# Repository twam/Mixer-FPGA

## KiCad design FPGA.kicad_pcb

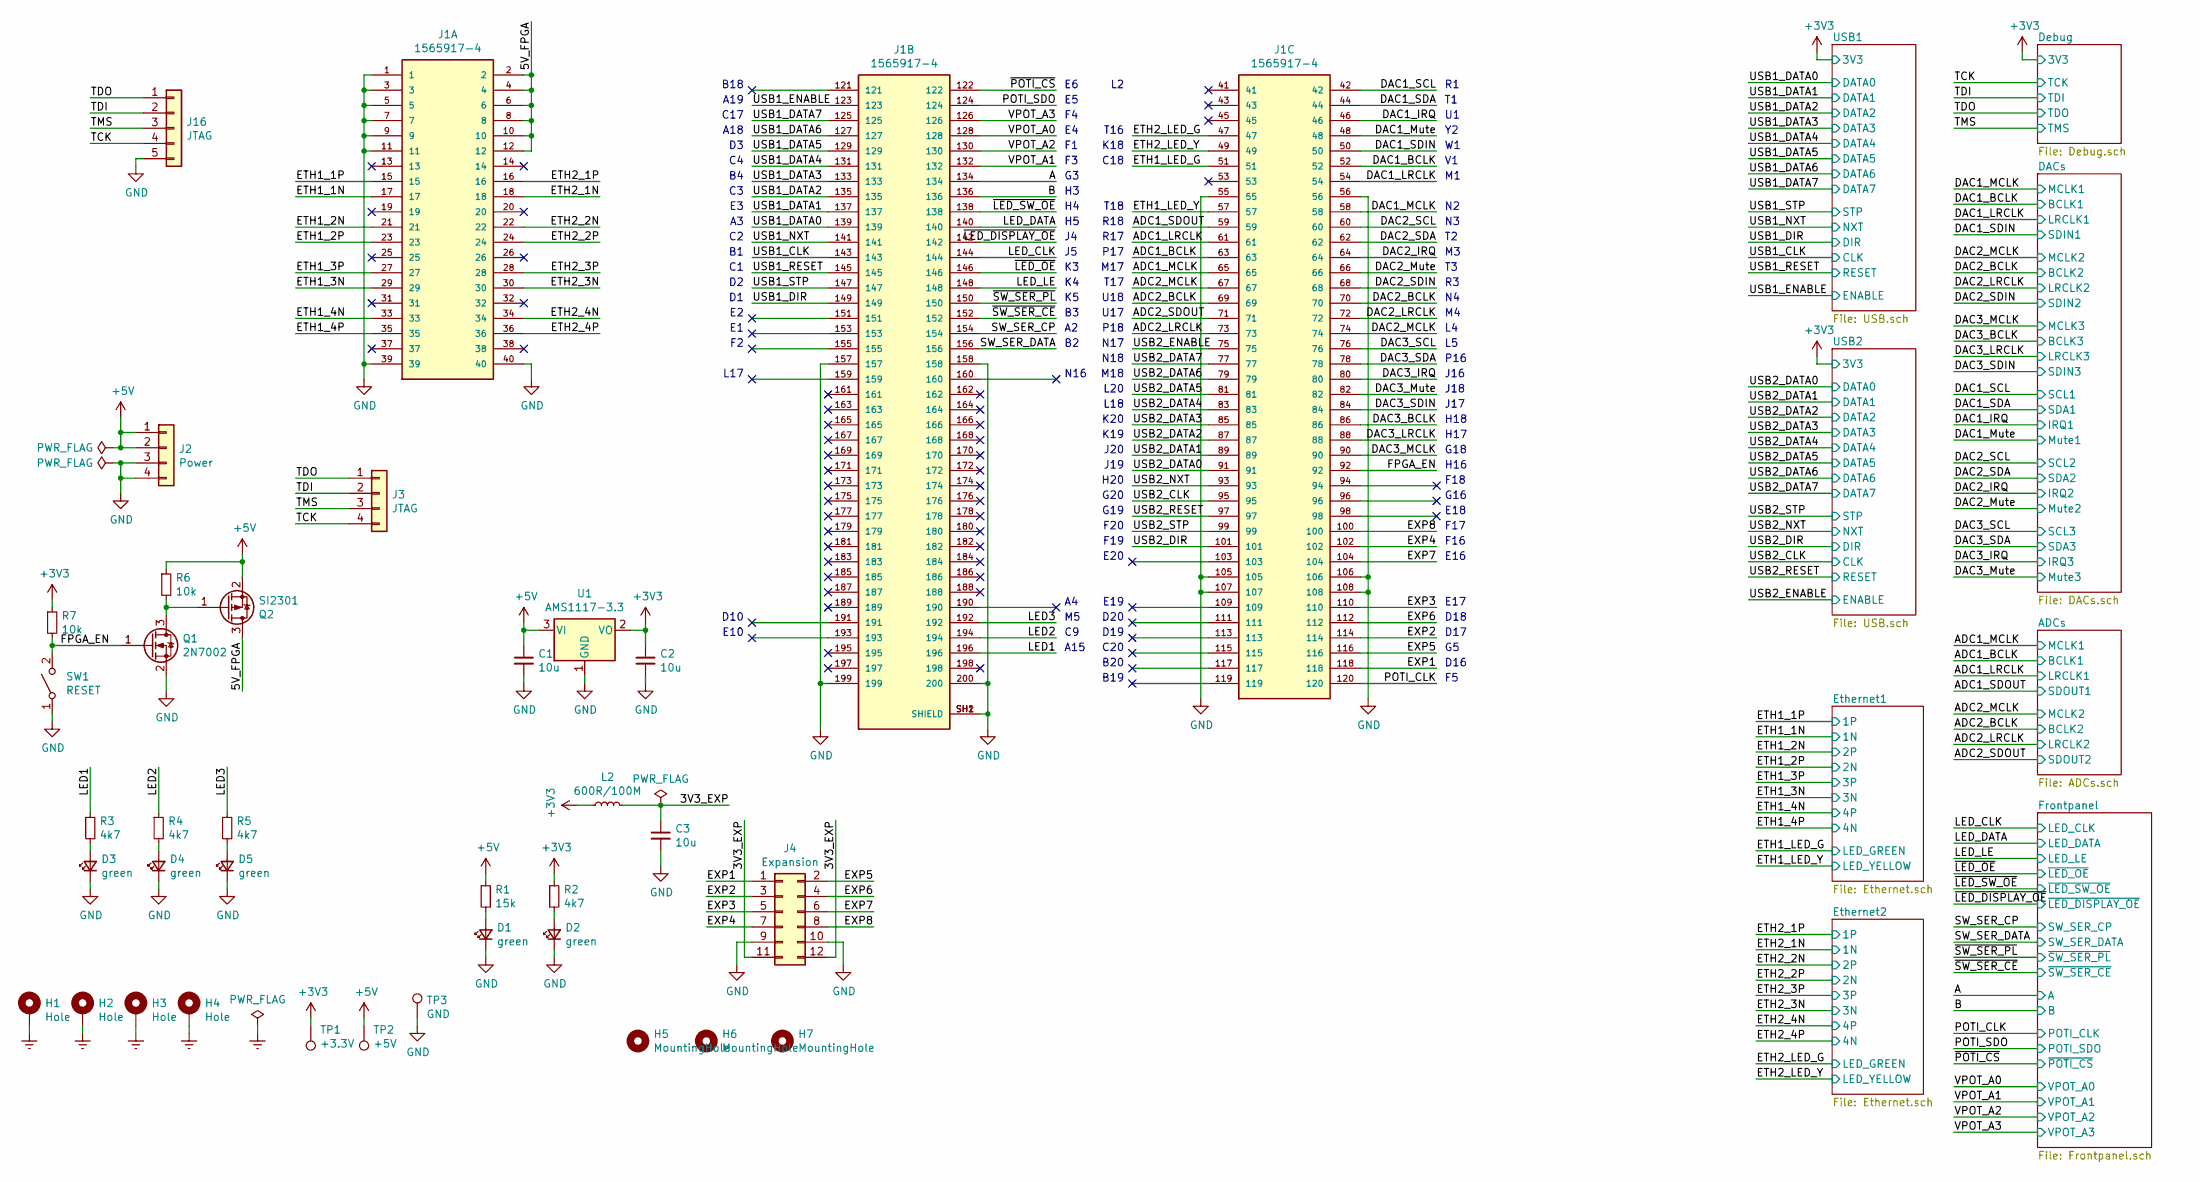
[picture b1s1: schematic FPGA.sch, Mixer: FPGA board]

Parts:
C1, C2, C3: 10u; C_0805_2012Metric; LCSC C15850
D1, D2, D3, D4, D5: green; LED_0603_1608Metric; LCSC C72043
H1, H2, H3, H4: Hole; MountingHole_2.7mm_M2.5_DIN965_Pad
H5, H6, H7: MountingHole; MountingHole_JLCPCB
J1: 1565917-4; TE_1565917-4
J2: Power; JST_VH_B4P-VH_1x04_P3.96mm_Vertical
J3: JTAG; PinHeader_1x04_P2.54mm_Vertical
J4: Expansion; PinHeader_2x06_P2.54mm_Vertical
J16: JTAG; PinHeader_1x05_P2.54mm_Vertical
L2: 600R/100M; L_0805_2012Metric; LCSC C1017
Q1: 2N7002; SOT-23; LCSC C8545
Q2: SI2301; SOT-23; LCSC C10487
R1: 15k; R_0603_1608Metric; LCSC C22809
R2, R3, R4, R5: 4k7; R_0603_1608Metric; LCSC C23162
R6, R7: 10k; R_0603_1608Metric; LCSC C25804
SW1: RESET; SW_SPST_XKB_TS-1187A-X-X-X; LCSC C318884
TP1: +3.3V; TestPoint_Pad_D1.5mm
TP2: +5V; TestPoint_Pad_D1.5mm
TP3: GND; TestPoint_Pad_D1.5mm
U1: AMS1117-3.3; SOT-223-3_TabPin2; LCSC C6186

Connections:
+3V3: C2.1, L2.1, R2.1, R7.1, TP1.1, U1.2 (VO); also elsewhere on the board
+5V: C1.1, J2.1, J2.2, Q2.2 (S), R1.1, R6.1, TP2.1, U1.3 (VI)
/3V3_EXP: C3.1, J4.11, J4.12, L2.2
/5V_FPGA: J1.2, J1.4, J1.6, J1.8, J1.10, J1.12, Q2.3 (D)
/A: J1.134; also elsewhere on the board
/ADC1_BCLK: J1.63; also elsewhere on the board
/ADC1_LRCLK: J1.61; also elsewhere on the board
/ADC1_MCLK: J1.65; also elsewhere on the board
/ADC1_SDOUT: J1.59; also elsewhere on the board
/ADC2_BCLK: J1.69; also elsewhere on the board
/ADC2_LRCLK: J1.73; also elsewhere on the board
/ADC2_MCLK: J1.67; also elsewhere on the board
/ADC2_SDOUT: J1.71; also elsewhere on the board
/B: J1.136; also elsewhere on the board
/DAC1_BCLK: J1.52; also elsewhere on the board
/DAC1_IRQ: J1.46; also elsewhere on the board
/DAC1_LRCLK: J1.54; also elsewhere on the board
/DAC1_MCLK: J1.58; also elsewhere on the board
/DAC1_Mute: J1.48; also elsewhere on the board
/DAC1_SCL: J1.42; also elsewhere on the board
/DAC1_SDA: J1.44; also elsewhere on the board
/DAC1_SDIN: J1.50; also elsewhere on the board
/DAC2_BCLK: J1.70; also elsewhere on the board
/DAC2_IRQ: J1.64; also elsewhere on the board
/DAC2_LRCLK: J1.72; also elsewhere on the board
/DAC2_MCLK: J1.74; also elsewhere on the board
/DAC2_Mute: J1.66; also elsewhere on the board
/DAC2_SCL: J1.60; also elsewhere on the board
/DAC2_SDA: J1.62; also elsewhere on the board
/DAC2_SDIN: J1.68; also elsewhere on the board
/DAC3_BCLK: J1.86; also elsewhere on the board
/DAC3_IRQ: J1.80; also elsewhere on the board
/DAC3_LRCLK: J1.88; also elsewhere on the board
/DAC3_MCLK: J1.90; also elsewhere on the board
/DAC3_Mute: J1.82; also elsewhere on the board
/DAC3_SCL: J1.76; also elsewhere on the board
/DAC3_SDA: J1.78; also elsewhere on the board
/DAC3_SDIN: J1.84; also elsewhere on the board
/ETH1_1N: J1.17; also elsewhere on the board
/ETH1_1P: J1.15; also elsewhere on the board
/ETH1_2N: J1.21; also elsewhere on the board
/ETH1_2P: J1.23; also elsewhere on the board
/ETH1_3N: J1.29; also elsewhere on the board
/ETH1_3P: J1.27; also elsewhere on the board
/ETH1_4N: J1.33; also elsewhere on the board
/ETH1_4P: J1.35; also elsewhere on the board
/ETH1_LED_G: J1.51; also elsewhere on the board
/ETH1_LED_Y: J1.57; also elsewhere on the board
/ETH2_1N: J1.18; also elsewhere on the board
/ETH2_1P: J1.16; also elsewhere on the board
/ETH2_2N: J1.22; also elsewhere on the board
/ETH2_2P: J1.24; also elsewhere on the board
/ETH2_3N: J1.30; also elsewhere on the board
/ETH2_3P: J1.28; also elsewhere on the board
/ETH2_4N: J1.34; also elsewhere on the board
/ETH2_4P: J1.36; also elsewhere on the board
/ETH2_LED_G: J1.47; also elsewhere on the board
/ETH2_LED_Y: J1.49; also elsewhere on the board
/EXP1: J1.118, J4.1
/EXP2: J1.114, J4.3
/EXP3: J1.110, J4.5
/EXP4: J1.102, J4.7
/EXP5: J1.116, J4.2
/EXP6: J1.112, J4.4
/EXP7: J1.104, J4.6
/EXP8: J1.100, J4.8
/FPGA_EN: J1.92, Q1.1 (G), R7.2, SW1.2 (B)
/LED1: J1.196, R3.1
/LED2: J1.194, R4.1
/LED3: J1.192, R5.1
/LED_CLK: J1.144; also elsewhere on the board
/LED_DATA: J1.140; also elsewhere on the board
/LED_LE: J1.148; also elsewhere on the board
/POTI_CLK: J1.120; also elsewhere on the board
/POTI_SDO: J1.124; also elsewhere on the board
/SW_SER_CP: J1.154; also elsewhere on the board
/SW_SER_DATA: J1.156; also elsewhere on the board
/TCK: J3.4, J16.4; also elsewhere on the board
/TDI: J3.2, J16.2; also elsewhere on the board
/TDO: J3.1, J16.1; also elsewhere on the board
/TMS: J3.3, J16.3; also elsewhere on the board
/USB1_CLK: J1.143; also elsewhere on the board
/USB1_DATA0: J1.139; also elsewhere on the board
/USB1_DATA1: J1.137; also elsewhere on the board
/USB1_DATA2: J1.135; also elsewhere on the board
/USB1_DATA3: J1.133; also elsewhere on the board
/USB1_DATA4: J1.131; also elsewhere on the board
/USB1_DATA5: J1.129; also elsewhere on the board
/USB1_DATA6: J1.127; also elsewhere on the board
/USB1_DATA7: J1.125; also elsewhere on the board
/USB1_DIR: J1.149; also elsewhere on the board
/USB1_ENABLE: J1.123; also elsewhere on the board
/USB1_NXT: J1.141; also elsewhere on the board
/USB1_RESET: J1.145; also elsewhere on the board
/USB1_STP: J1.147; also elsewhere on the board
/USB2_CLK: J1.95; also elsewhere on the board
/USB2_DATA0: J1.91; also elsewhere on the board
/USB2_DATA1: J1.89; also elsewhere on the board
/USB2_DATA2: J1.87; also elsewhere on the board
/USB2_DATA3: J1.85; also elsewhere on the board
/USB2_DATA4: J1.83; also elsewhere on the board
/USB2_DATA5: J1.81; also elsewhere on the board
/USB2_DATA6: J1.79; also elsewhere on the board
/USB2_DATA7: J1.77; also elsewhere on the board
/USB2_DIR: J1.101; also elsewhere on the board
/USB2_ENABLE: J1.75; also elsewhere on the board
/USB2_NXT: J1.93; also elsewhere on the board
/USB2_RESET: J1.97; also elsewhere on the board
/USB2_STP: J1.99; also elsewhere on the board
/VPOT_A0: J1.128; also elsewhere on the board
/VPOT_A1: J1.132; also elsewhere on the board
/VPOT_A2: J1.130; also elsewhere on the board
/VPOT_A3: J1.126; also elsewhere on the board
/~LED_DISPLAY_OE: J1.142; also elsewhere on the board
/~LED_OE: J1.146; also elsewhere on the board
/~LED_SW_OE: J1.138; also elsewhere on the board
/~POTI_CS: J1.122; also elsewhere on the board
/~SW_SER_CE: J1.152; also elsewhere on the board
/~SW_SER_PL: J1.150; also elsewhere on the board
Earth: H1.1, H2.1, H3.1, H4.1; also elsewhere on the board
GND: C1.2, C2.2, C3.2, D1.1 (K), D2.1 (K), D3.1 (K), D4.1 (K), D5.1 (K), J1.1, J1.3, J1.5, J1.7, J1.9, J1.11, J1.39, J1.40, J1.55, J1.56, J1.105, J1.106, J1.107, J1.108, J1.157, J1.158, J1.199, J1.200, J1.SH1 (SHIELD), J1.SH2 (SHIELD), J2.3, J2.4, J4.9, J4.10, J16.5, Q1.2 (S), SW1.1 (A), TP3.1, U1.1 (GND); also elsewhere on the board
unnamed: D1.2 (A), R1.2
unnamed: D2.2 (A), R2.2
unnamed: D3.2 (A), R3.2
unnamed: D4.2 (A), R4.2
unnamed: D5.2 (A), R5.2
unnamed: Q1.3 (D), Q2.1 (G), R6.2

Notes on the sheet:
K18
C18
T18
R18
R17
P17
M17
T17
U18
U17
P18
N17
N18
M18
L20
L18
K20
K19
J20
J19
H20
G20
G19
F20
F19
E20
E19
D20
D19
C20
B20
B19
D16
D17
D18
E17
E16
F16
F17
E18

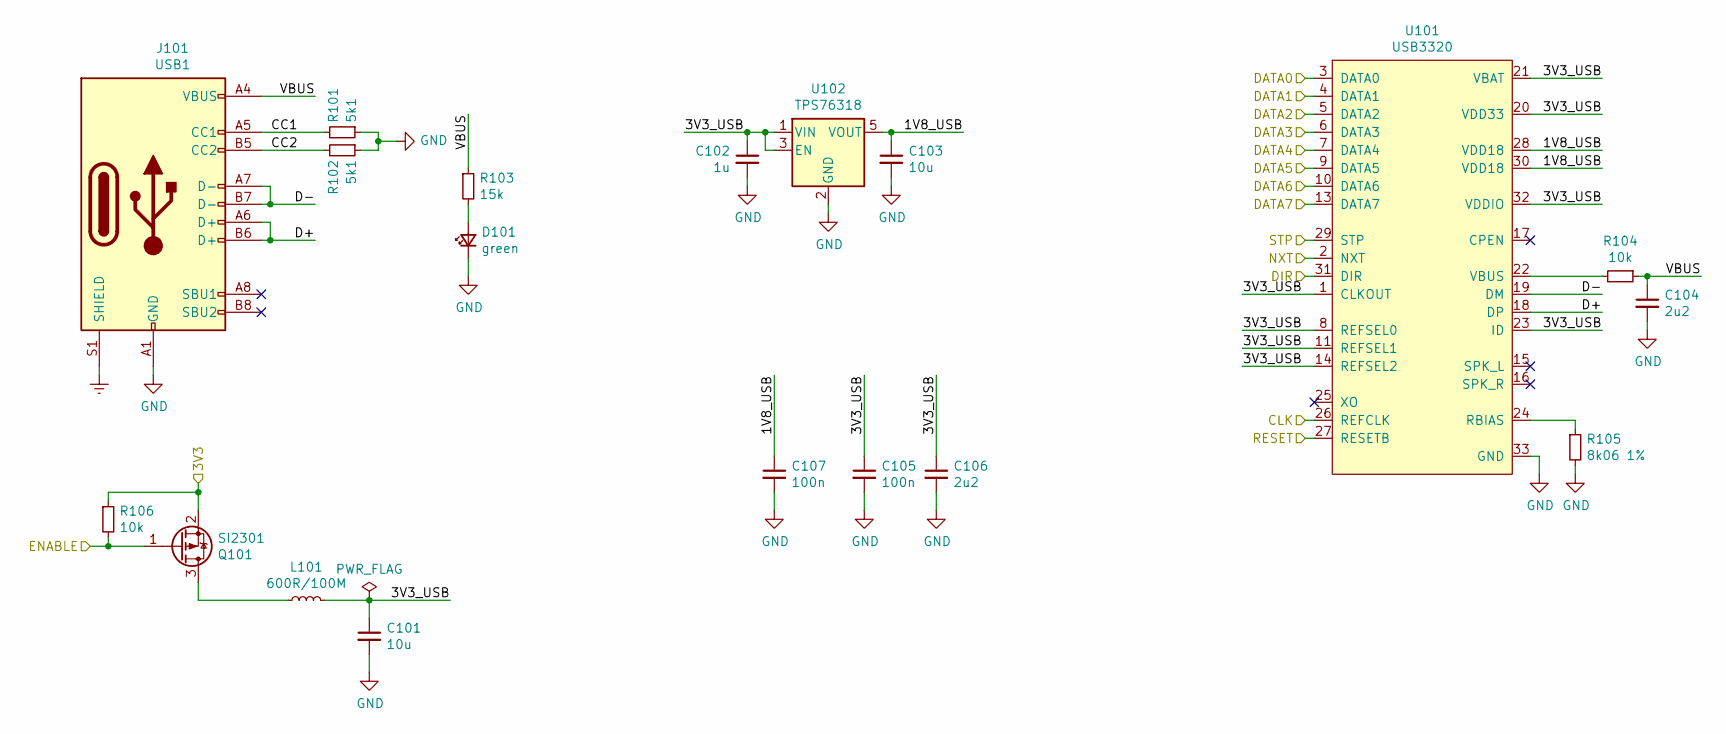
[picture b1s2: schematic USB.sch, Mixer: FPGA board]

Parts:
C101: 10u; C_0805_2012Metric; LCSC C15850
C102: 1u; C_0603_1608Metric; LCSC C15849
C103: 10u; C_0603_1608Metric; LCSC C19702
C104, C106: 2u2; C_0603_1608Metric; LCSC C23630
C105, C107: 100n; C_0603_1608Metric; LCSC C14663
D101: green; LED_0603_1608Metric; LCSC C72043
J101: USB1; USB_C_Receptacle_XKB_U262-16XN-4BVC11; LCSC C165948
L101: 600R/100M; L_0805_2012Metric; LCSC C1017
Q101: SI2301; SOT-23; LCSC C10487
R101, R102: 5k1; R_0603_1608Metric; LCSC C23186
R103: 15k; R_0603_1608Metric; LCSC C22809
R104, R106: 10k; R_0603_1608Metric; LCSC C25804
R105: 8k06 1%; R_0603_1608Metric; LCSC C23112
U101: USB3320; QFN-32-1EP_5x5mm_P0.5mm_EP3.3x3.3mm; LCSC C132156
U102: TPS76318; SOT-23-5; LCSC C7099

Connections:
+3V3: Q101.2 (S), R106.1; also elsewhere on the board
/USB1/1V8_USB: C103.1, C107.1, U101.28 (VDD18), U101.30 (VDD18), U102.5 (VOUT)
/USB1/3V3_USB: C101.1, C102.1, C105.1, C106.1, L101.2, U101.1 (CLKOUT), U101.8 (REFSEL0), U101.11 (REFSEL1), U101.14 (REFSEL2), U101.20 (VDD33), U101.21 (VBAT), U101.23 (ID), U101.32 (VDDIO), U102.1 (VIN), U102.3 (EN)
/USB1/CC1: J101.A5 (CC1), R101.2
/USB1/CC2: J101.B5 (CC2), R102.2
/USB1/D+: J101.A6 (D+), J101.B6 (D+), U101.18 (DP)
/USB1/D-: J101.A7 (D-), J101.B7 (D-), U101.19 (DM)
/USB1/VBUS: C104.1, J101.A4 (VBUS), J101.A9 (VBUS), J101.B4 (VBUS), J101.B9 (VBUS), R103.1, R104.1
/USB1_CLK: U101.26 (REFCLK); also elsewhere on the board
/USB1_DATA0: U101.3 (DATA0); also elsewhere on the board
/USB1_DATA1: U101.4 (DATA1); also elsewhere on the board
/USB1_DATA2: U101.5 (DATA2); also elsewhere on the board
/USB1_DATA3: U101.6 (DATA3); also elsewhere on the board
/USB1_DATA4: U101.7 (DATA4); also elsewhere on the board
/USB1_DATA5: U101.9 (DATA5); also elsewhere on the board
/USB1_DATA6: U101.10 (DATA6); also elsewhere on the board
/USB1_DATA7: U101.13 (DATA7); also elsewhere on the board
/USB1_DIR: U101.31 (DIR); also elsewhere on the board
/USB1_ENABLE: Q101.1 (G), R106.2; also elsewhere on the board
/USB1_NXT: U101.2 (NXT); also elsewhere on the board
/USB1_RESET: U101.27 (RESETB); also elsewhere on the board
/USB1_STP: U101.29 (STP); also elsewhere on the board
Earth: J101.S1 (SHIELD); also elsewhere on the board
GND: C101.2, C102.2, C103.2, C104.2, C105.2, C106.2, C107.2, D101.1 (K), J101.A1 (GND), J101.A12 (GND), J101.B1 (GND), J101.B12 (GND), R101.1, R102.1, R105.2, U101.33 (GND), U102.2 (GND); also elsewhere on the board
unnamed: D101.2 (A), R103.2
unnamed: L101.1, Q101.3 (D)
unnamed: R104.2, U101.22 (VBUS)
unnamed: R105.1, U101.24 (RBIAS)

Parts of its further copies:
C201: 10u; C_0805_2012Metric; LCSC C15850
C202: 1u; C_0603_1608Metric; LCSC C15849
C203: 10u; C_0603_1608Metric; LCSC C19702
C204, C206: 2u2; C_0603_1608Metric; LCSC C23630
C205, C207: 100n; C_0603_1608Metric; LCSC C14663
D201: green; LED_0603_1608Metric; LCSC C72043
J201: USB1; USB_C_Receptacle_XKB_U262-16XN-4BVC11; LCSC C165948
L201: 600R/100M; L_0805_2012Metric; LCSC C1017
Q201: SI2301; SOT-23; LCSC C10487
R201, R202: 5k1; R_0603_1608Metric; LCSC C23186
R203: 15k; R_0603_1608Metric; LCSC C22809
R204, R206: 10k; R_0603_1608Metric; LCSC C25804
R205: 8k06 1%; R_0603_1608Metric; LCSC C23112
U201: USB3320; QFN-32-1EP_5x5mm_P0.5mm_EP3.3x3.3mm; LCSC C132156
U202: TPS76318; SOT-23-5; LCSC C7099

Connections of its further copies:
+3V3: Q201.2 (S), R206.1; also elsewhere on the board
/USB2/1V8_USB: C203.1, C207.1, U201.28 (VDD18), U201.30 (VDD18), U202.5 (VOUT)
/USB2/3V3_USB: C201.1, C202.1, C205.1, C206.1, L201.2, U201.1 (CLKOUT), U201.8 (REFSEL0), U201.11 (REFSEL1), U201.14 (REFSEL2), U201.20 (VDD33), U201.21 (VBAT), U201.23 (ID), U201.32 (VDDIO), U202.1 (VIN), U202.3 (EN)
/USB2/CC1: J201.A5 (CC1), R201.2
/USB2/CC2: J201.B5 (CC2), R202.2
/USB2/D+: J201.A6 (D+), J201.B6 (D+), U201.18 (DP)
/USB2/D-: J201.A7 (D-), J201.B7 (D-), U201.19 (DM)
/USB2/VBUS: C204.1, J201.A4 (VBUS), J201.A9 (VBUS), J201.B4 (VBUS), J201.B9 (VBUS), R203.1, R204.1
/USB2_CLK: U201.26 (REFCLK); also elsewhere on the board
/USB2_DATA0: U201.3 (DATA0); also elsewhere on the board
/USB2_DATA1: U201.4 (DATA1); also elsewhere on the board
/USB2_DATA2: U201.5 (DATA2); also elsewhere on the board
/USB2_DATA3: U201.6 (DATA3); also elsewhere on the board
/USB2_DATA4: U201.7 (DATA4); also elsewhere on the board
/USB2_DATA5: U201.9 (DATA5); also elsewhere on the board
/USB2_DATA6: U201.10 (DATA6); also elsewhere on the board
/USB2_DATA7: U201.13 (DATA7); also elsewhere on the board
/USB2_DIR: U201.31 (DIR); also elsewhere on the board
/USB2_ENABLE: Q201.1 (G), R206.2; also elsewhere on the board
/USB2_NXT: U201.2 (NXT); also elsewhere on the board
/USB2_RESET: U201.27 (RESETB); also elsewhere on the board
/USB2_STP: U201.29 (STP); also elsewhere on the board
Earth: J201.S1 (SHIELD); also elsewhere on the board
GND: C201.2, C202.2, C203.2, C204.2, C205.2, C206.2, C207.2, D201.1 (K), J201.A1 (GND), J201.A12 (GND), J201.B1 (GND), J201.B12 (GND), R201.1, R202.1, R205.2, U201.33 (GND), U202.2 (GND); also elsewhere on the board
unnamed: D201.2 (A), R203.2
unnamed: L201.1, Q201.3 (D)
unnamed: R204.2, U201.22 (VBUS)
unnamed: R205.1, U201.24 (RBIAS)

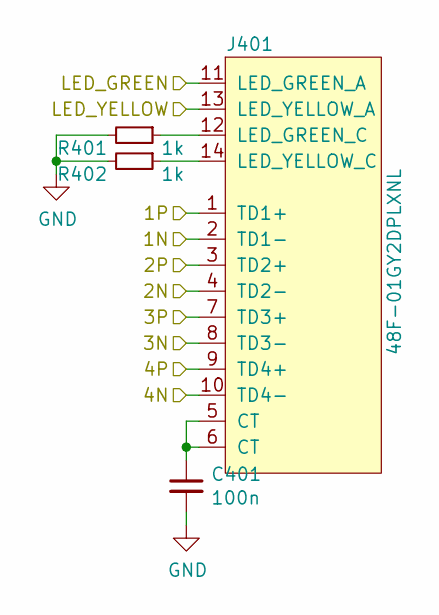
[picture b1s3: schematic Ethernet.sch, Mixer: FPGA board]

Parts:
C301: 100n; C_0603_1608Metric; LCSC C14663
J301: 48F-01GY2DPLXNL; LCSC C123172
R301, R302: 1k; R_0603_1608Metric; LCSC C21190

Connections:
/ETH1_1N: J301.2 (TD1-); also elsewhere on the board
/ETH1_1P: J301.1 (TD1+); also elsewhere on the board
/ETH1_2N: J301.3 (TD2+); also elsewhere on the board
/ETH1_2P: J301.4 (TD2-); also elsewhere on the board
/ETH1_3N: J301.8 (TD3-); also elsewhere on the board
/ETH1_3P: J301.7 (TD3+); also elsewhere on the board
/ETH1_4N: J301.9 (TD4+); also elsewhere on the board
/ETH1_4P: J301.10 (TD4-); also elsewhere on the board
/ETH1_LED_G: J301.11 (LED_GREEN_A); also elsewhere on the board
/ETH1_LED_Y: J301.13 (LED_YELLOW_A); also elsewhere on the board
GND: C301.2, R301.2, R302.2; also elsewhere on the board
unnamed: C301.1, J301.5 (CT), J301.6 (CT)
unnamed: J301.12 (LED_GREEN_C), R301.1
unnamed: J301.14 (LED_YELLOW_C), R302.1

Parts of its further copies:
C401: 100n; C_0603_1608Metric; LCSC C14663
J401: 48F-01GY2DPLXNL; LCSC C123172
R401, R402: 1k; R_0603_1608Metric; LCSC C21190

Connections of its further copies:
/ETH2_1N: J401.2 (TD1-); also elsewhere on the board
/ETH2_1P: J401.1 (TD1+); also elsewhere on the board
/ETH2_2N: J401.3 (TD2+); also elsewhere on the board
/ETH2_2P: J401.4 (TD2-); also elsewhere on the board
/ETH2_3N: J401.8 (TD3-); also elsewhere on the board
/ETH2_3P: J401.7 (TD3+); also elsewhere on the board
/ETH2_4N: J401.9 (TD4+); also elsewhere on the board
/ETH2_4P: J401.10 (TD4-); also elsewhere on the board
/ETH2_LED_G: J401.11 (LED_GREEN_A); also elsewhere on the board
/ETH2_LED_Y: J401.13 (LED_YELLOW_A); also elsewhere on the board
GND: C401.2, R401.2, R402.2; also elsewhere on the board
unnamed: C401.1, J401.5 (CT), J401.6 (CT)
unnamed: J401.12 (LED_GREEN_C), R401.1
unnamed: J401.14 (LED_YELLOW_C), R402.1

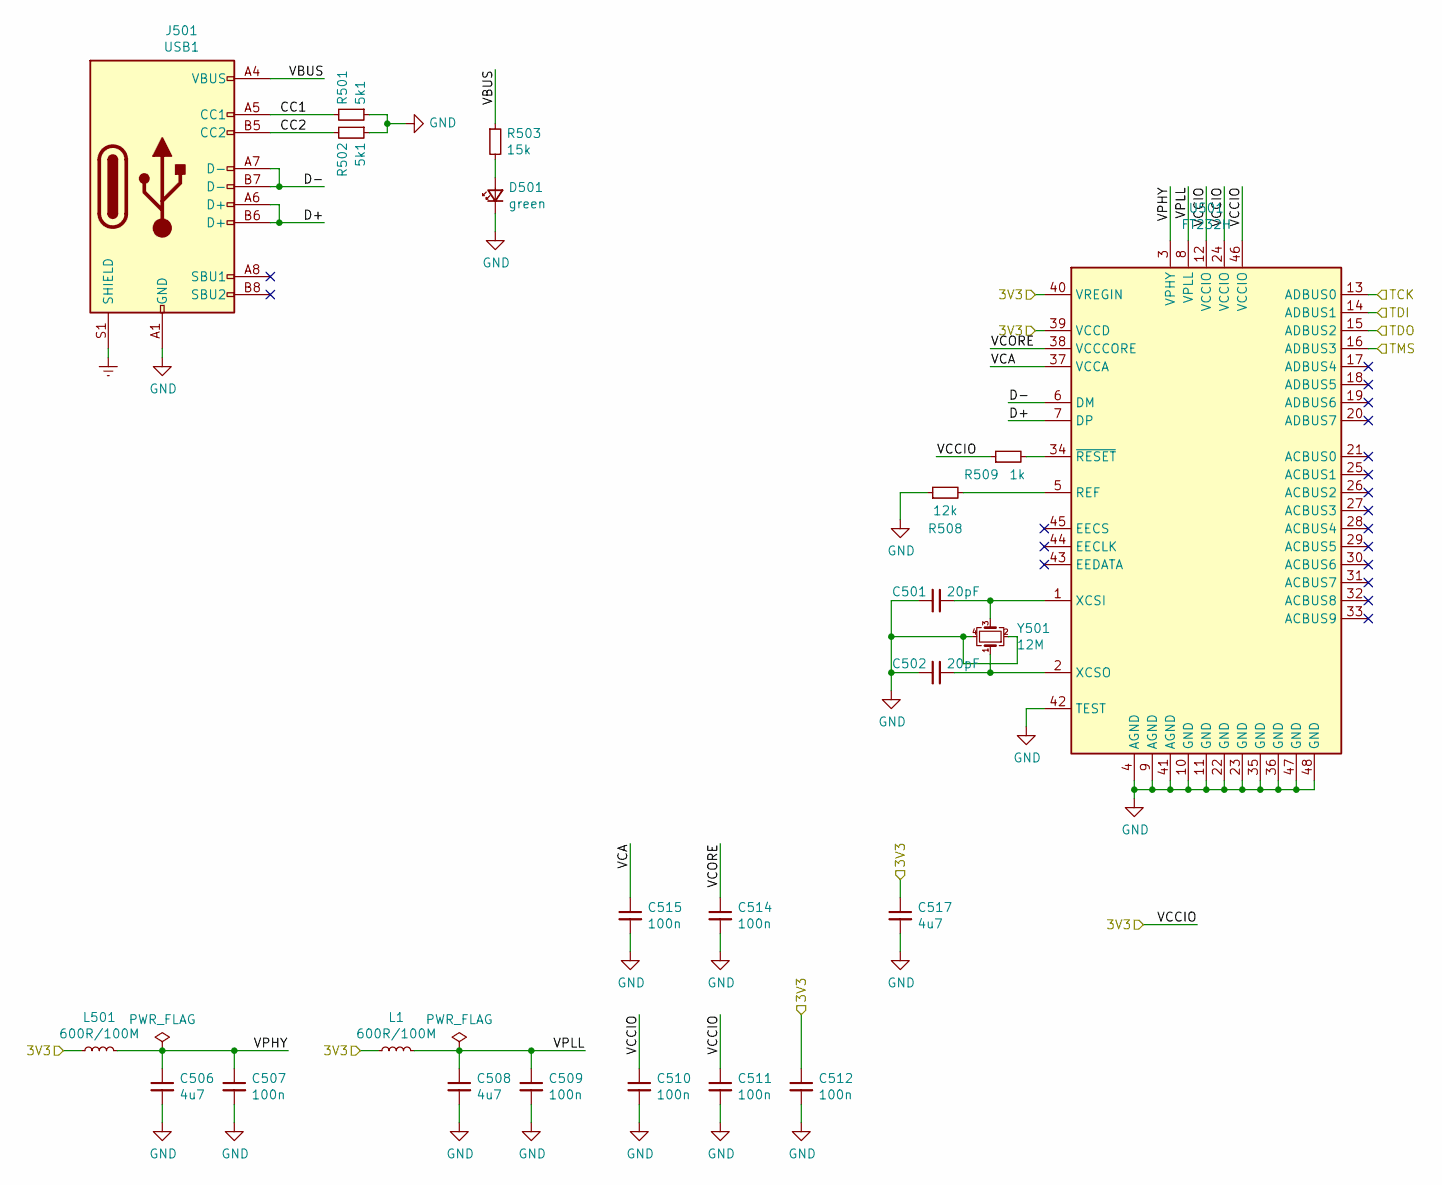
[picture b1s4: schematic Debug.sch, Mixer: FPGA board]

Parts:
C501, C502: 20pF; C_0603_1608Metric; LCSC C1648
C506, C508, C517: 4u7; C_0603_1608Metric; LCSC C19666
C507, C509, C510, C511, C512, C514, C515: 100n; C_0603_1608Metric; LCSC C14663
D501: green; LED_0603_1608Metric; LCSC C72043
J501: USB1; USB_C_Receptacle_XKB_U262-16XN-4BVC11; LCSC C165948
L1, L501: 600R/100M; L_0805_2012Metric; LCSC C1017
R501, R502: 5k1; R_0603_1608Metric; LCSC C23186
R503: 15k; R_0603_1608Metric; LCSC C22809
R508: 12k; R_0603_1608Metric; LCSC C22790
R509: 1k; R_0603_1608Metric; LCSC C21190
U501: FT232H; LQFP-48_7x7mm_P0.5mm; LCSC C51997
Y501: 12M; Crystal_SMD_3225-4Pin_3.2x2.5mm; LCSC C9002

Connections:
+3V3: C510.1, C511.1, C512.1, C517.1, L1.1, L501.1, R509.1, U501.12 (VCCIO), U501.24 (VCCIO), U501.39 (VCCD), U501.40 (VREGIN), U501.46 (VCCIO); also elsewhere on the board
/Debug/CC1: J501.A5 (CC1), R501.2
/Debug/CC2: J501.B5 (CC2), R502.2
/Debug/D+: J501.A6 (D+), J501.B6 (D+), U501.7 (DP)
/Debug/D-: J501.A7 (D-), J501.B7 (D-), U501.6 (DM)
/Debug/VBUS: J501.A4 (VBUS), J501.A9 (VBUS), J501.B4 (VBUS), J501.B9 (VBUS), R503.1
/Debug/VCA: C515.1, U501.37 (VCCA)
/Debug/VCORE: C514.1, U501.38 (VCCCORE)
/Debug/VPHY: C506.1, C507.1, L501.2, U501.3 (VPHY)
/Debug/VPLL: C508.1, C509.1, L1.2, U501.8 (VPLL)
/TCK: U501.13 (ADBUS0); also elsewhere on the board
/TDI: U501.14 (ADBUS1); also elsewhere on the board
/TDO: U501.15 (ADBUS2); also elsewhere on the board
/TMS: U501.16 (ADBUS3); also elsewhere on the board
Earth: J501.S1 (SHIELD); also elsewhere on the board
GND: C501.2, C502.2, C506.2, C507.2, C508.2, C509.2, C510.2, C511.2, C512.2, C514.2, C515.2, C517.2, D501.1 (K), J501.A1 (GND), J501.A12 (GND), J501.B1 (GND), J501.B12 (GND), R501.1, R502.1, R508.1, U501.4 (AGND), U501.9 (AGND), U501.10 (GND), U501.11 (GND), U501.22 (GND), U501.23 (GND), U501.35 (GND), U501.36 (GND), U501.41 (AGND), U501.42 (TEST), U501.47 (GND), U501.48 (GND), Y501.2, Y501.4; also elsewhere on the board
unnamed: C501.1, U501.1 (XCSI), Y501.3
unnamed: C502.1, U501.2 (XCSO), Y501.1
unnamed: D501.2 (A), R503.2
unnamed: R508.2, U501.5 (REF)
unnamed: R509.2, U501.34 (~RESET)

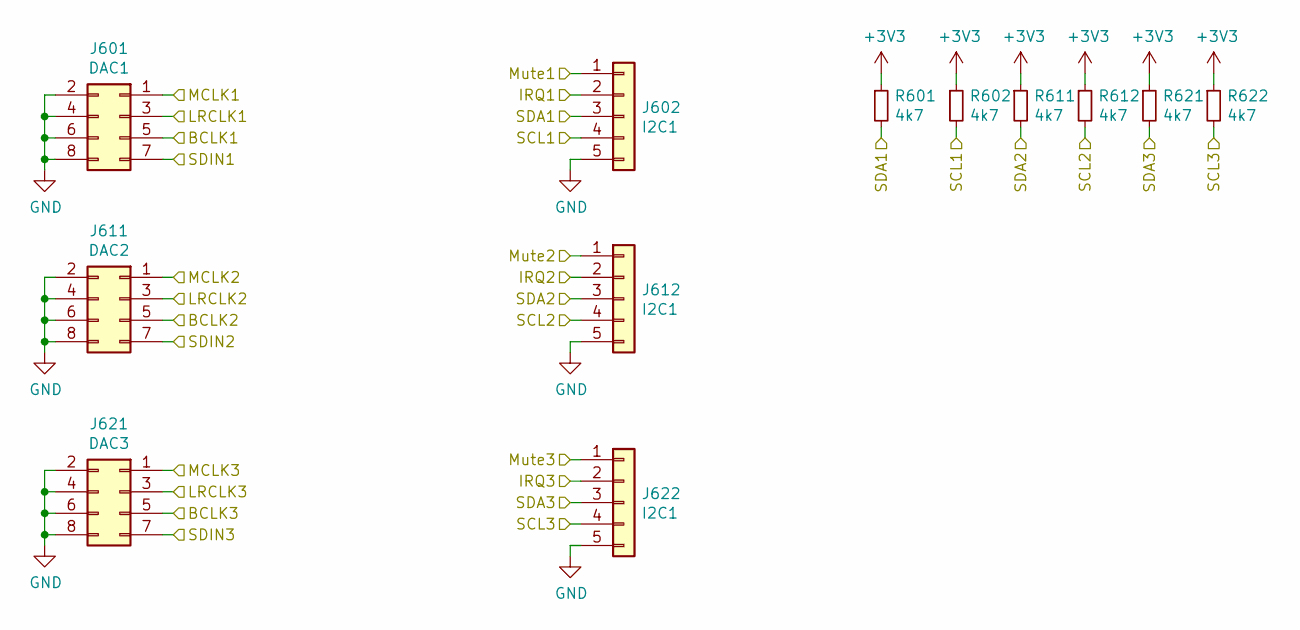
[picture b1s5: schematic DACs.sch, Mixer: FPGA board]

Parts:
J601: DAC1; PinHeader_2x04_P2.54mm_Vertical
J602, J612, J622: I2C1; PinHeader_1x05_P2.54mm_Vertical
J611: DAC2; PinHeader_2x04_P2.54mm_Vertical
J621: DAC3; PinHeader_2x04_P2.54mm_Vertical
R601, R602, R611, R612, R621, R622: 4k7; R_0603_1608Metric; LCSC C23162

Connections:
+3V3: R601.1, R602.1, R611.1, R612.1, R621.1, R622.1; also elsewhere on the board
/DAC1_BCLK: J601.5; also elsewhere on the board
/DAC1_IRQ: J602.2; also elsewhere on the board
/DAC1_LRCLK: J601.3; also elsewhere on the board
/DAC1_MCLK: J601.1; also elsewhere on the board
/DAC1_Mute: J602.1; also elsewhere on the board
/DAC1_SCL: J602.4, R602.2; also elsewhere on the board
/DAC1_SDA: J602.3, R601.2; also elsewhere on the board
/DAC1_SDIN: J601.7; also elsewhere on the board
/DAC2_BCLK: J611.5; also elsewhere on the board
/DAC2_IRQ: J612.2; also elsewhere on the board
/DAC2_LRCLK: J611.3; also elsewhere on the board
/DAC2_MCLK: J611.1; also elsewhere on the board
/DAC2_Mute: J612.1; also elsewhere on the board
/DAC2_SCL: J612.4, R612.2; also elsewhere on the board
/DAC2_SDA: J612.3, R611.2; also elsewhere on the board
/DAC2_SDIN: J611.7; also elsewhere on the board
/DAC3_BCLK: J621.5; also elsewhere on the board
/DAC3_IRQ: J622.2; also elsewhere on the board
/DAC3_LRCLK: J621.3; also elsewhere on the board
/DAC3_MCLK: J621.1; also elsewhere on the board
/DAC3_Mute: J622.1; also elsewhere on the board
/DAC3_SCL: J622.4, R622.2; also elsewhere on the board
/DAC3_SDA: J622.3, R621.2; also elsewhere on the board
/DAC3_SDIN: J621.7; also elsewhere on the board
GND: J601.2, J601.4, J601.6, J601.8, J602.5, J611.2, J611.4, J611.6, J611.8, J612.5, J621.2, J621.4, J621.6, J621.8, J622.5; also elsewhere on the board

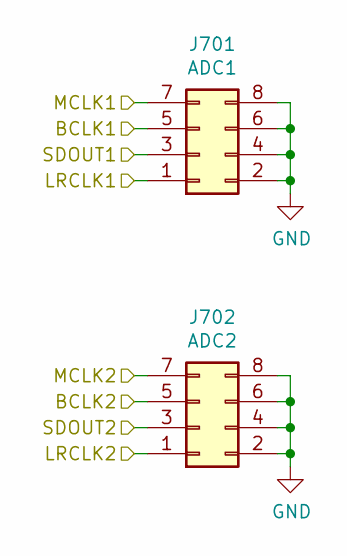
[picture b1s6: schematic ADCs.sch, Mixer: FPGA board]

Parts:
J701: ADC1; PinHeader_2x04_P2.54mm_Vertical
J702: ADC2; PinHeader_2x04_P2.54mm_Vertical

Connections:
/ADC1_BCLK: J701.5; also elsewhere on the board
/ADC1_LRCLK: J701.1; also elsewhere on the board
/ADC1_MCLK: J701.7; also elsewhere on the board
/ADC1_SDOUT: J701.3; also elsewhere on the board
/ADC2_BCLK: J702.5; also elsewhere on the board
/ADC2_LRCLK: J702.1; also elsewhere on the board
/ADC2_MCLK: J702.7; also elsewhere on the board
/ADC2_SDOUT: J702.3; also elsewhere on the board
GND: J701.2, J701.4, J701.6, J701.8, J702.2, J702.4, J702.6, J702.8; also elsewhere on the board

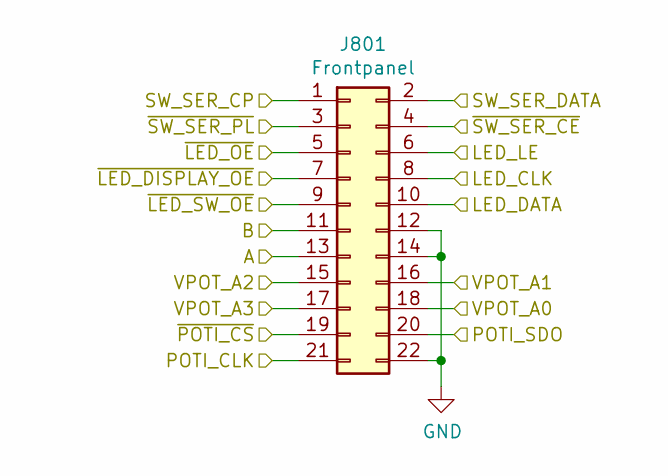
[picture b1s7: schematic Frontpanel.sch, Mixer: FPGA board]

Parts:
J801: Frontpanel; PinHeader_2x11_P2.54mm_Vertical

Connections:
/A: J801.13; also elsewhere on the board
/B: J801.11; also elsewhere on the board
/LED_CLK: J801.8; also elsewhere on the board
/LED_DATA: J801.10; also elsewhere on the board
/LED_LE: J801.6; also elsewhere on the board
/POTI_CLK: J801.21; also elsewhere on the board
/POTI_SDO: J801.20; also elsewhere on the board
/SW_SER_CP: J801.1; also elsewhere on the board
/SW_SER_DATA: J801.2; also elsewhere on the board
/VPOT_A0: J801.18; also elsewhere on the board
/VPOT_A1: J801.16; also elsewhere on the board
/VPOT_A2: J801.15; also elsewhere on the board
/VPOT_A3: J801.17; also elsewhere on the board
/~LED_DISPLAY_OE: J801.7; also elsewhere on the board
/~LED_OE: J801.5; also elsewhere on the board
/~LED_SW_OE: J801.9; also elsewhere on the board
/~POTI_CS: J801.19; also elsewhere on the board
/~SW_SER_CE: J801.4; also elsewhere on the board
/~SW_SER_PL: J801.3; also elsewhere on the board
GND: J801.12, J801.14, J801.22; also elsewhere on the board

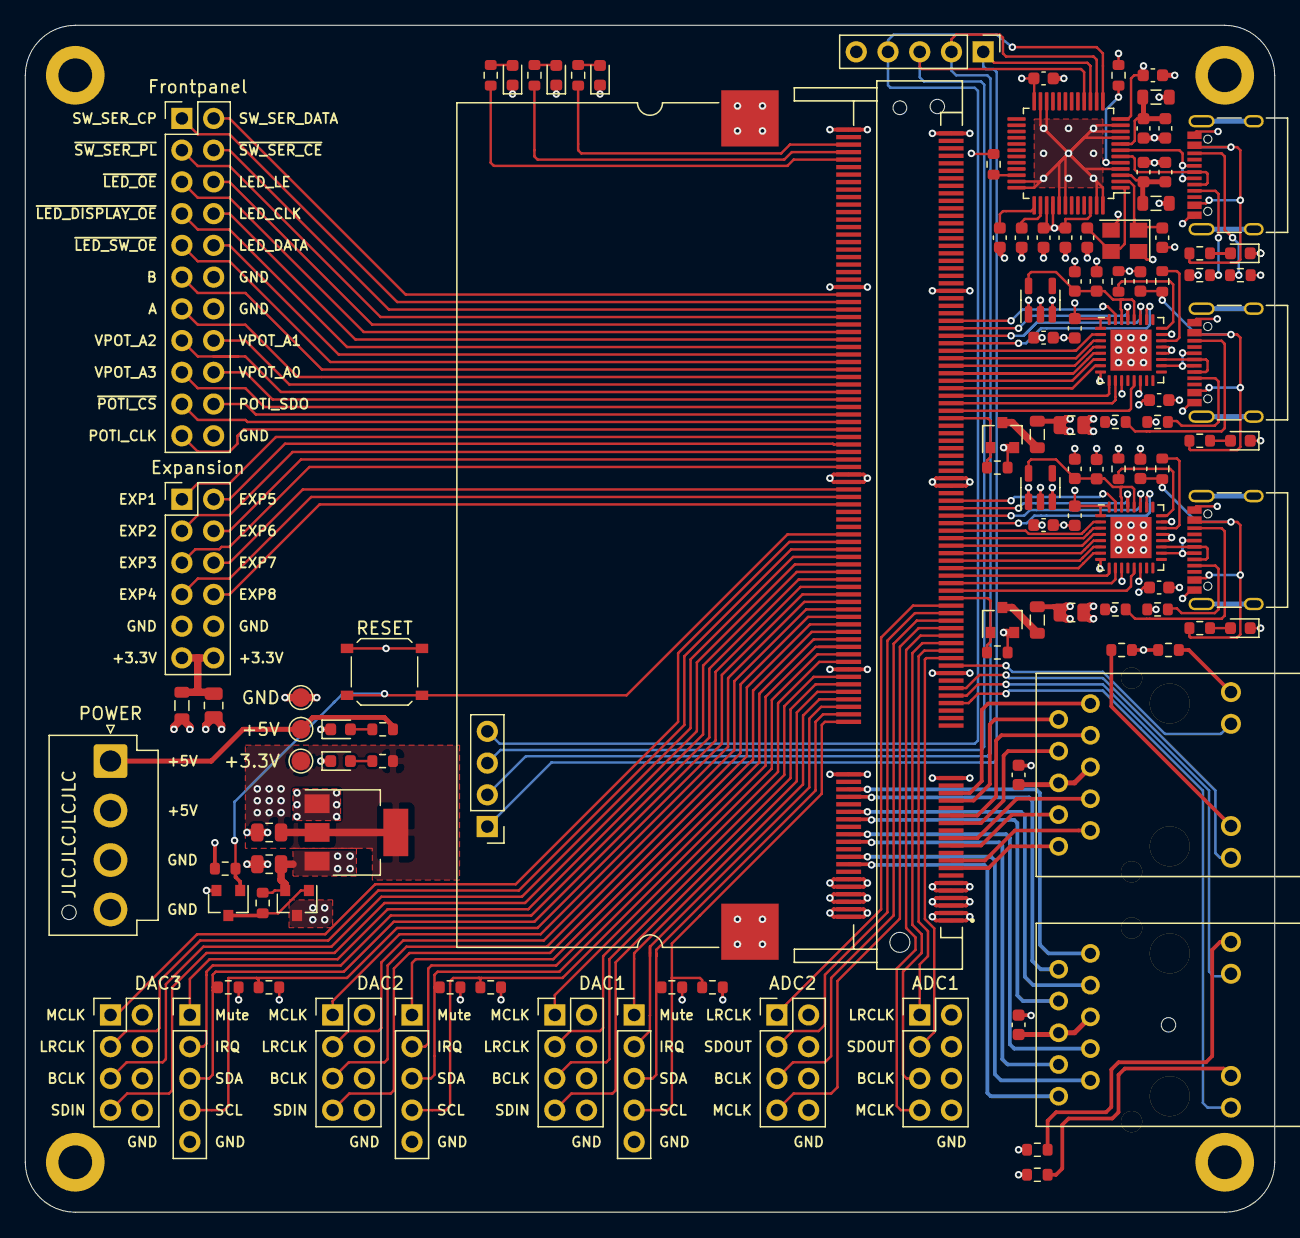
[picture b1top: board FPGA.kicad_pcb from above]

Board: 4 copper layers, 100.0 x 95.0 mm, 119 parts (0 on the bottom side), 169 nets.

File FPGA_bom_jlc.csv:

"Comment","Designator","Footprint","LCSC Part #"
"10u","C2,C1,C3,C101,C201","C_0805_2012Metric","C15850"
"1u","C102,C202","C_0603_1608Metric","C15849"
"10u","C103,C203","C_0603_1608Metric","C19702"
"2u2","C104,C106,C204,C206","C_0603_1608Metric","C23630"
"100n","C107,C105,C207,C205,C301,C401,C507,C509,C510,C511,C512,C514,C515","C_0603_1608Metric","C14663"
"20pF","C501,C502","C_0603_1608Metric","C1648"
"4u7","C506,C508,C517","C_0603_1608Metric","C19666"
"green","D1,D2,D3,D4,D5,D101,D201,D501","LED_0603_1608Metric","C72043"
"USB1","J101,J201,J501","USB_C_Receptacle_XKB_U262-16XN-4BVC11","C165948"
"48F-01GY2DPLXNL","J301,J401","48F-01GY2DPLXNL","C123172"
"600R/100M","L2,L101,L201,L501,L1","L_0805_2012Metric","C1017"
"2N7002","Q1","SOT-23","C8545"
"SI2301","Q2,Q101,Q201","SOT-23","C10487"
"15k","R1,R103,R203,R503","R_0603_1608Metric","C22809"
"4k7","R2,R3,R4,R5,R601,R602,R611,R612,R621,R622","R_0603_1608Metric","C23162"
"10k","R6,R7,R104,R106,R204,R206","R_0603_1608Metric","C25804"
"5k1","R101,R102,R201,R202,R501,R502","R_0603_1608Metric","C23186"
"8k06 1%","R105,R205","R_0603_1608Metric","C23112"
"1k","R302,R301,R402,R401,R509","R_0603_1608Metric","C21190"
"12k","R508","R_0603_1608Metric","C22790"
"RESET","SW1","SW_SPST_XKB_TS-1187A-X-X-X","C318884"
"AMS1117-3.3","U1","SOT-223-3_TabPin2","C6186"
"USB3320","U101,U201","QFN-32-1EP_5x5mm_P0.5mm_EP3.3x3.3mm","C132156"
"TPS76318","U102,U202","SOT-23-5","C7099"
"FT232H","U501","LQFP-48_7x7mm_P0.5mm","C51997"
"12M","Y501","Crystal_SMD_3225-4Pin_3.2x2.5mm","C9002"

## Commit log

2021-04-16 Initial commit. Rev 1.

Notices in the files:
ADCs.sch:
License: CC-BY-SA 4.0
